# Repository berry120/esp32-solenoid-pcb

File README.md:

# esp32-solenoid-pcb

PCB for solenoid control (using a ESP-WROOM32 module.)

Just an Eagle project here, and the associated Gerbers (generated with the SeeedStudio cam file.)

Use at your own risk!

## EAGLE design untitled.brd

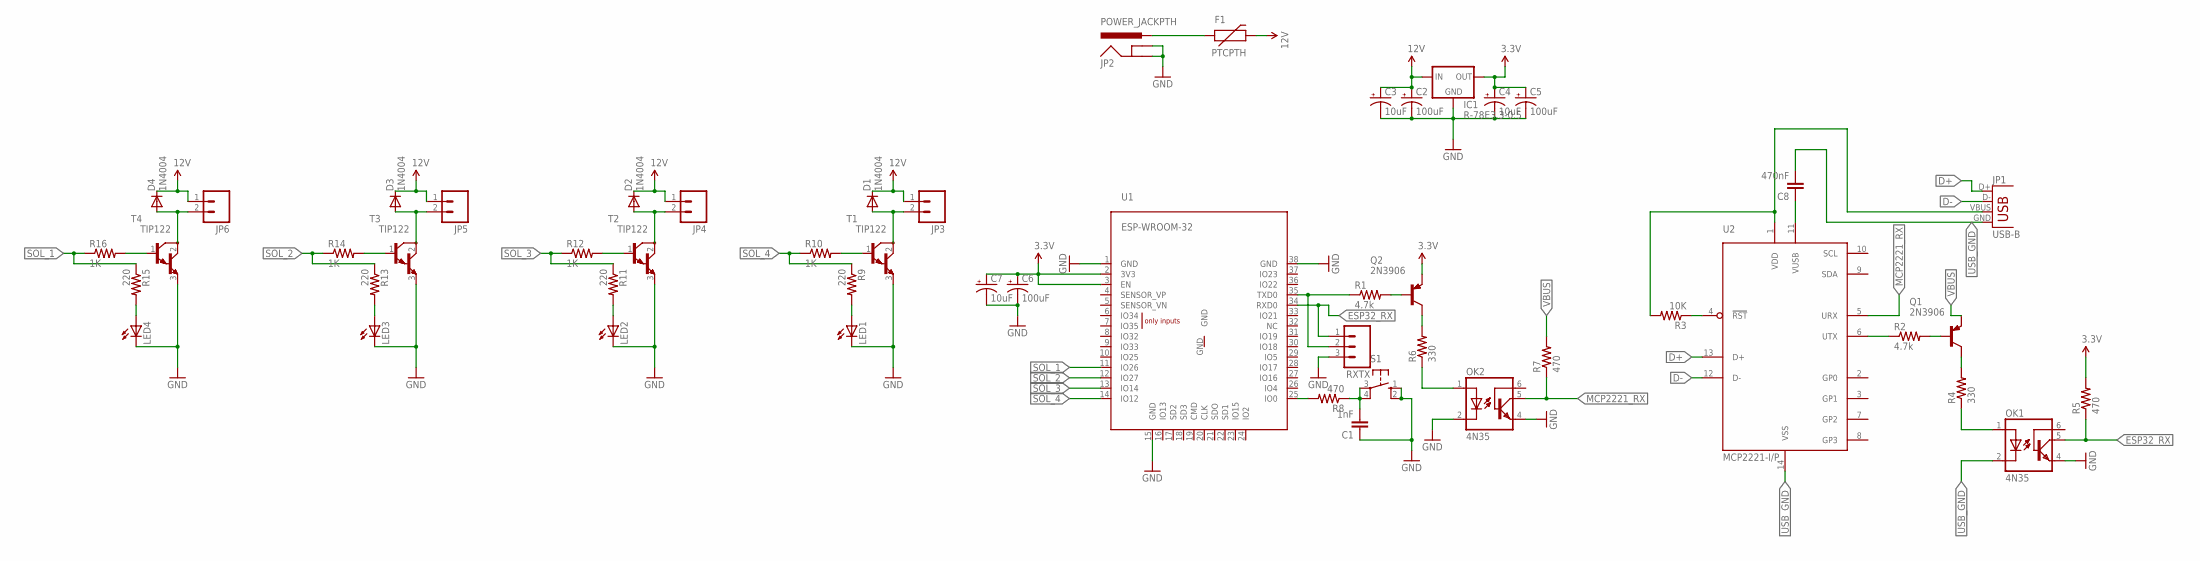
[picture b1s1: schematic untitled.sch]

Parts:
C1: 1nF; CAP-PTH-SMALL-KIT
C2, C5, C6: 100uF; CPOL-RADIAL-100UF-25V
C3, C4, C7: 10uF; CPOL-RADIAL-100UF-25V
C8: 470nF; CAP-PTH-SMALLEZ; MPN MCBU5471K5
D1, D2, D3, D4: 1N4004; DO41-10
F1: PTCPTH; PTC
IC1: R-78E3.3-0.5; SIP3
JP1: USB-B; USB-B-PTH; MPN USB-B-S-RA.
JP2: POWER_JACKPTH; POWER_JACK_PTH; MPN DC10A
JP3, JP4, JP5, JP6: M02LOCK_LONGPADS; 1X02_LOCK_LONGPADS
LED1, LED2, LED3, LED4: LED3MM
OK1, OK2: 4N35; DIL06
Q1, Q2: 2N3906; TO92; MPN 2N3906
R1, R2: 4.7k; AXIAL-0.3; MPN MCRE000045
R3: 10K; AXIAL-0.3; MPN MCMF006FF1002A50
R4, R6: 330; AXIAL-0.3; MPN MCRE000031
R5, R7, R8: 470; AXIAL-0.3; MPN MCRE000033
R9, R11, R13, R15: 220; AXIAL-0.3; MPN MCRE000033
R10, R12, R14, R16: 1K; AXIAL-0.3; MPN MCRE000033
RXTX: M03LONGPADS; 1X03_LONGPADS
S1: 10-XX; B3F-10XX
T1, T2, T3, T4: TIP122; TO220
U1: ESP-WROOM-32
U2: MCP2221-I/P; DIL14; MPN MCP2221-I/P

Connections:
3.3V: C4.1 (+), C5.1 (+), C6.1 (+), C7.1 (+), IC1.3 (OUT), Q2.3 (E), R5.P$2 (2), U1.2 (3V3), U1.3 (EN)
12V: C2.1 (+), C3.1 (+), D1.C, D2.C, D3.C, D4.C, F1.P$2 (2), IC1.1 (IN), JP3.1, JP4.1, JP5.1, JP6.1
D+: JP1.D+, U2.13 (D+)
D-: JP1.D-, U2.12 (D-)
ESP32_RX: OK1.5 (COL), R5.P$1 (1), RXTX.1, U1.34 (RXD0)
GND: C1.1, C2.2 (-), C3.2 (-), C4.2 (-), C5.2 (-), C6.2 (-), C7.2 (-), IC1.2 (GND), JP2.GND, JP2.GNDBREAK, LED1.K (C), LED2.K (C), LED3.K (C), LED4.K (C), OK1.4 (EMI), OK2.2 (C), OK2.4 (EMI), RXTX.3, S1.1 (S), S1.2 (S1), T1.3 (E), T2.3 (E), T3.3 (E), T4.3 (E), U1.1 (GND), U1.15 (GND), U1.38 (GND)
MCP2221_RX: OK2.5 (COL), R7.P$1 (1), U2.5 (URX)
unnamed: Q1.1 (C), R4.P$2 (2)
unnamed: R1.P$1 (1), RXTX.2, U1.35 (TXD0)
unnamed: C8.1, U2.11 (VUSB)
unnamed: Q2.2 (B), R1.P$2 (2)
unnamed: R3.P$1 (1), U2.4 (!RST)
unnamed: R2.P$1 (1), U2.6 (UTX)
unnamed: Q1.2 (B), R2.P$2 (2)
unnamed: OK1.1 (A), R4.P$1 (1)
unnamed: Q2.1 (C), R6.P$2 (2)
unnamed: OK2.1 (A), R6.P$1 (1)
unnamed: R8.P$2 (2), U1.25 (IO0)
unnamed: D1.A, JP3.2, T1.2 (C)
unnamed: LED1.A, R9.P$2 (2)
unnamed: R10.P$2 (2), T1.1 (B)
unnamed: D2.A, JP4.2, T2.2 (C)
unnamed: LED2.A, R11.P$2 (2)
unnamed: R12.P$2 (2), T2.1 (B)
unnamed: D3.A, JP5.2, T3.2 (C)
unnamed: LED3.A, R13.P$2 (2)
unnamed: R14.P$2 (2), T3.1 (B)
unnamed: D4.A, JP6.2, T4.2 (C)
unnamed: LED4.A, R15.P$2 (2)
unnamed: R16.P$2 (2), T4.1 (B)
unnamed: F1.P$1 (1), JP2.PWR
RXTX: C1.2, R8.P$1 (1), S1.3, S1.4 (P1)
SOL_1: R15.P$1 (1), R16.P$1 (1), U1.11 (IO26)
SOL_2: R13.P$1 (1), R14.P$1 (1), U1.12 (IO27)
SOL_3: R11.P$1 (1), R12.P$1 (1), U1.13 (IO14)
SOL_4: R9.P$1 (1), R10.P$1 (1), U1.14 (IO12)
USB_GND: C8.2, JP1.GND, OK1.2 (C), U2.14 (VSS)
VBUS: JP1.VBUS, Q1.3 (E), R3.P$2 (2), R7.P$2 (2), U2.1 (VDD)

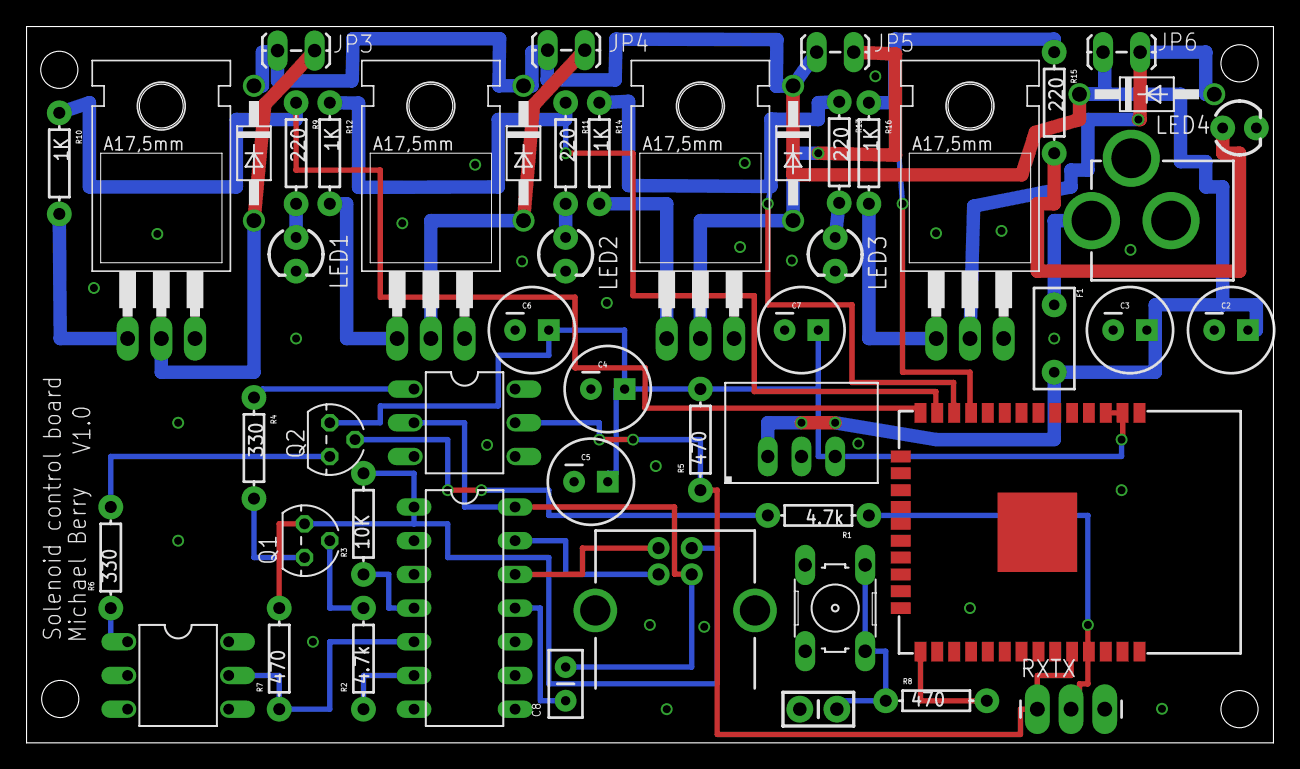
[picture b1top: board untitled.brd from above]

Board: 2 copper layers, 94.0 x 54.0 mm, 52 parts (0 on the bottom side), 38 nets.

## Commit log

2018-06-19 Add Eagle files
2019-07-16 Add Codacy badge

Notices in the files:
parts and their libraries:
SparkFun: Licensing: CC v3.0 Share-Alike You are welcome to use this library for commercial purposes.
SparkFun-Capacitors: Licensing: Creative Commons ShareAlike 4.0 International - https://creativecommons.org/licenses/by-sa/4.0
r-78xx_10: (c) 2015 Samuel Lourenço
